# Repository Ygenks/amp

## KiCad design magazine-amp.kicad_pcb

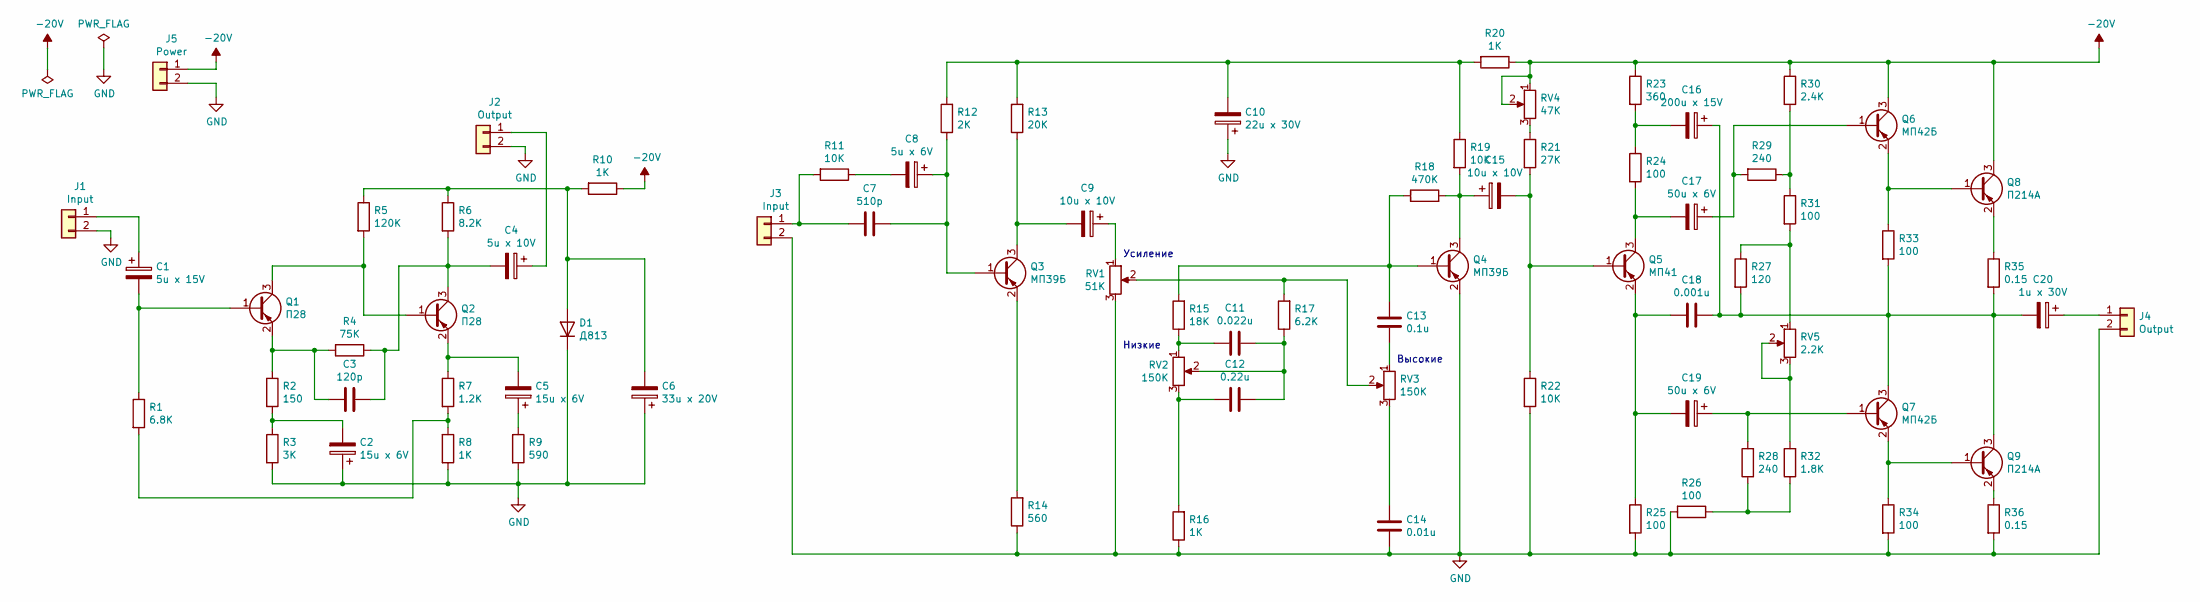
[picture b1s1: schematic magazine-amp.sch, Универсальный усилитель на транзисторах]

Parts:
C1: 5u x 15V; CP_Radial_D4.0mm_P2.00mm
C2, C5: 15u x 6V; CP_Radial_D5.0mm_P2.00mm
C3: 120p; C_Rect_L4.6mm_W3.8mm_P2.50mm_MKS02_FKP02
C4: 5u x 10V; CP_Radial_D4.0mm_P2.00mm
C6: 33u x 20V; CP_Radial_D5.0mm_P2.00mm
C7: 510p; C_Disc_D4.7mm_W2.5mm_P5.00mm
C8: 5u x 6V; CP_Radial_D4.0mm_P2.00mm
C9, C15: 10u x 10V; CP_Radial_D4.0mm_P2.00mm
C10: 22u x 30V; CP_Radial_D5.0mm_P2.00mm
C11: 0.022u; C_Disc_D10.0mm_W2.5mm_P5.00mm
C12: 0.22u; C_Disc_D14.5mm_W5.0mm_P7.50mm
C13: 0.1u; C_Disc_D14.5mm_W5.0mm_P7.50mm
C14: 0.01u; C_Disc_D7.5mm_W4.4mm_P5.00mm
C16: 200u x 15V; CP_Radial_D8.0mm_P3.50mm
C17, C19: 50u x 6V; CP_Radial_D5.0mm_P2.00mm
C18: 0.001u; C_Rect_L4.6mm_W3.8mm_P2.50mm_MKS02_FKP02
C20: 1u x 30V; CP_Radial_D5.0mm_P2.00mm
D1: Д813; D_DO-201_P15.24mm_Horizontal
J1, J3: Input; PinSocket_1x02_P2.54mm_Vertical
J2, J4: Output; PinSocket_1x02_P2.54mm_Vertical
J5: Power; PinSocket_1x02_P2.54mm_Vertical
Q1, Q2: П28; TO-11-3
Q3, Q4: МП39Б; TO-5-3
Q5: МП41; TO-5-3
Q6, Q7: МП42Б; TO-5-3
Q8, Q9: П214А; TO-5-3
R1: 6.8K; R_Axial_DIN0309_L9.0mm_D3.2mm_P12.70mm_Horizontal
R2: 150; R_Axial_DIN0309_L9.0mm_D3.2mm_P12.70mm_Horizontal
R3: 3K; R_Axial_DIN0309_L9.0mm_D3.2mm_P12.70mm_Horizontal
R4: 75K; R_Axial_DIN0309_L9.0mm_D3.2mm_P12.70mm_Horizontal
R5: 120K; R_Axial_DIN0309_L9.0mm_D3.2mm_P12.70mm_Horizontal
R6: 8.2K; R_Axial_DIN0309_L9.0mm_D3.2mm_P12.70mm_Horizontal
R7: 1.2K; R_Axial_DIN0309_L9.0mm_D3.2mm_P12.70mm_Horizontal
R8, R10, R16, R20: 1K; R_Axial_DIN0309_L9.0mm_D3.2mm_P12.70mm_Horizontal
R9: 590; R_Axial_DIN0309_L9.0mm_D3.2mm_P12.70mm_Horizontal
R11, R19, R22: 10K; R_Axial_DIN0309_L9.0mm_D3.2mm_P12.70mm_Horizontal
R12: 2K; R_Axial_DIN0309_L9.0mm_D3.2mm_P12.70mm_Horizontal
R13: 20K; R_Axial_DIN0309_L9.0mm_D3.2mm_P12.70mm_Horizontal
R14: 560; R_Axial_DIN0309_L9.0mm_D3.2mm_P12.70mm_Horizontal
R15: 18K; R_Axial_DIN0309_L9.0mm_D3.2mm_P12.70mm_Horizontal
R17: 6.2K; R_Axial_DIN0309_L9.0mm_D3.2mm_P12.70mm_Horizontal
R18: 470K; R_Axial_DIN0309_L9.0mm_D3.2mm_P12.70mm_Horizontal
R21: 27K; R_Axial_DIN0309_L9.0mm_D3.2mm_P12.70mm_Horizontal
R23: 360; R_Axial_DIN0309_L9.0mm_D3.2mm_P12.70mm_Horizontal
R24, R25, R26, R31, R33, R34: 100; R_Axial_DIN0309_L9.0mm_D3.2mm_P12.70mm_Horizontal
R27: 120; R_Axial_DIN0309_L9.0mm_D3.2mm_P12.70mm_Horizontal
R28, R29: 240; R_Axial_DIN0309_L9.0mm_D3.2mm_P12.70mm_Horizontal
R30: 2.4K; R_Axial_DIN0309_L9.0mm_D3.2mm_P12.70mm_Horizontal
R32: 1.8K; R_Axial_DIN0309_L9.0mm_D3.2mm_P12.70mm_Horizontal
R35, R36: 0.15; R_Axial_DIN0918_L18.0mm_D9.0mm_P25.40mm_Horizontal
RV1: 51K; PinSocket_1x03_P2.54mm_Vertical
RV2, RV3: 150K; PinSocket_1x03_P2.54mm_Vertical
RV4: 47K; PinSocket_1x03_P2.54mm_Vertical
RV5: 2.2K; PinSocket_1x03_P2.54mm_Vertical

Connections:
-20V: J5.1, Q6.3 (C), Q8.3 (C), R10.1, R20.1, R23.1, R30.1, RV4.1, RV4.2
GND: C2.1, C6.1, C10.1, C14.2, D1.1 (K), J1.2, J2.2, J3.2, J4.2, J5.2, Q4.2 (E), R3.2, R8.2, R9.2, R14.1, R16.1, R22.2, R25.2, R26.2, R34.2, R36.2, RV1.3
unnamed: C1.1, J1.1
unnamed: C1.2, Q1.1 (B), R1.1
unnamed: C2.2, R2.2, R3.1
unnamed: C3.1, C4.2, Q2.3 (C), R4.1, R6.2
unnamed: C3.2, Q1.2 (E), R2.1, R4.2
unnamed: C4.1, J2.1
unnamed: C5.1, R9.1
unnamed: C5.2, Q2.2 (E), R7.1
unnamed: C6.2, D1.2 (A), R5.1, R6.1, R10.2
unnamed: C7.1, C8.1, Q3.1 (B), R12.1
unnamed: C7.2, J3.1, R11.2
unnamed: C8.2, R11.1
unnamed: C9.1, RV1.1
unnamed: C9.2, Q3.3 (C), R13.1
unnamed: C10.2, R12.2, R13.2, R19.1, R20.2
unnamed: C11.1, C12.1, R17.1, RV2.2
unnamed: C11.2, R15.1, RV2.1
unnamed: C12.2, R16.2, RV2.3
unnamed: C13.1, Q4.1 (B), R15.2, R18.1
unnamed: C13.2, RV3.1
unnamed: C14.1, RV3.3
unnamed: C15.1, Q4.3 (C), R18.2, R19.2
unnamed: C15.2, Q5.1 (B), R21.2, R22.1
unnamed: C16.1, C18.1, C20.2, Q7.3 (C), Q9.3 (C), R27.2, R33.2, R35.2
unnamed: C16.2, R23.2, R24.1
unnamed: C17.1, Q6.1 (B), R29.2
unnamed: C17.2, Q5.3 (C), R24.2
unnamed: C18.2, C19.2, Q5.2 (E), R25.1
unnamed: C19.1, Q7.1 (B), R28.2
unnamed: C20.1, J4.1
unnamed: Q1.3 (C), Q2.1 (B), R5.2
unnamed: Q3.2 (E), R14.2
unnamed: Q6.2 (E), Q8.1 (B), R33.1
unnamed: Q7.2 (E), Q9.1 (B), R34.1
unnamed: Q8.2 (E), R35.1
unnamed: Q9.2 (E), R36.1
unnamed: R1.2, R7.2, R8.1
unnamed: R17.2, RV1.2, RV3.2
unnamed: R21.1, RV4.3
unnamed: R26.1, R28.1, R32.1
unnamed: R27.1, R31.2, RV5.1
unnamed: R29.1, R30.2, R31.1
unnamed: R32.2, RV5.2, RV5.3

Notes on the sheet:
Усиление
Низкие
Высокие

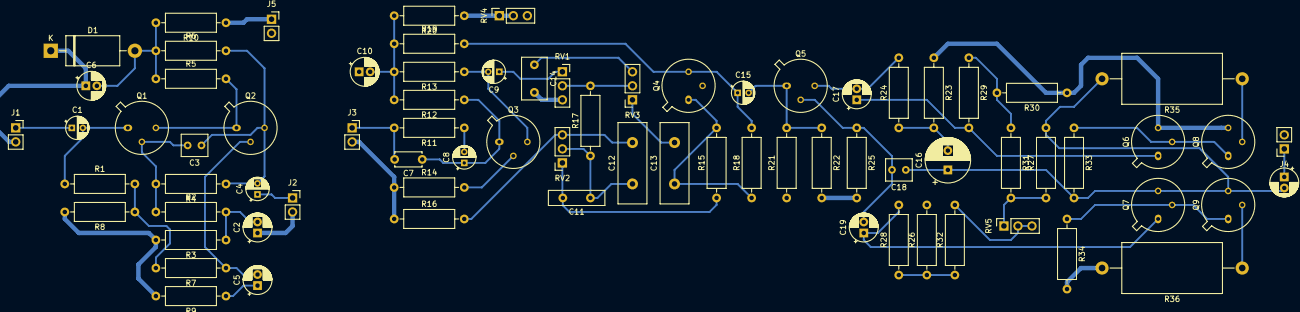
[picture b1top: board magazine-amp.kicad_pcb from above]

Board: 2 copper layers, 76 parts (0 on the bottom side), 45 nets.

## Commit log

2020-02-04 Start drawing top part of schematic
2020-03-12 Finish top schematics
2020-03-22 Fix component values
2020-04-12 Finish schematics
2020-04-12 Add PCB
2021-05-21 Fix power nets
2021-05-23 Add preamp schematic
2021-05-23 Assign footprints to components
2021-05-26 Route preamp
2021-05-26 Route power amplifier
2021-05-26 Fix ground traces
